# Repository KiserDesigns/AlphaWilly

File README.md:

Firmware built on this commit of Vial:

https://github.com/vial-kb/vial-qmk/commit/d4976853a3d72a370eeb24f6754e1618b5deb3bd

Newer Vial and QMK versions will need modification to firmware files.

PCB designed with Kicad 6.0.10, using various footprints and symbols with undetermined origin.

AlphaWetPCB/ is the Kicad PCB files

WilliamPlate/ is the Kicad Plate files

"William Plate.dxf" is the plate outline for laser cutting

alphawilly/ contains Vial and QMK firmware source

.uf2 file is the default firmware to flash.

GPL 3.0 License

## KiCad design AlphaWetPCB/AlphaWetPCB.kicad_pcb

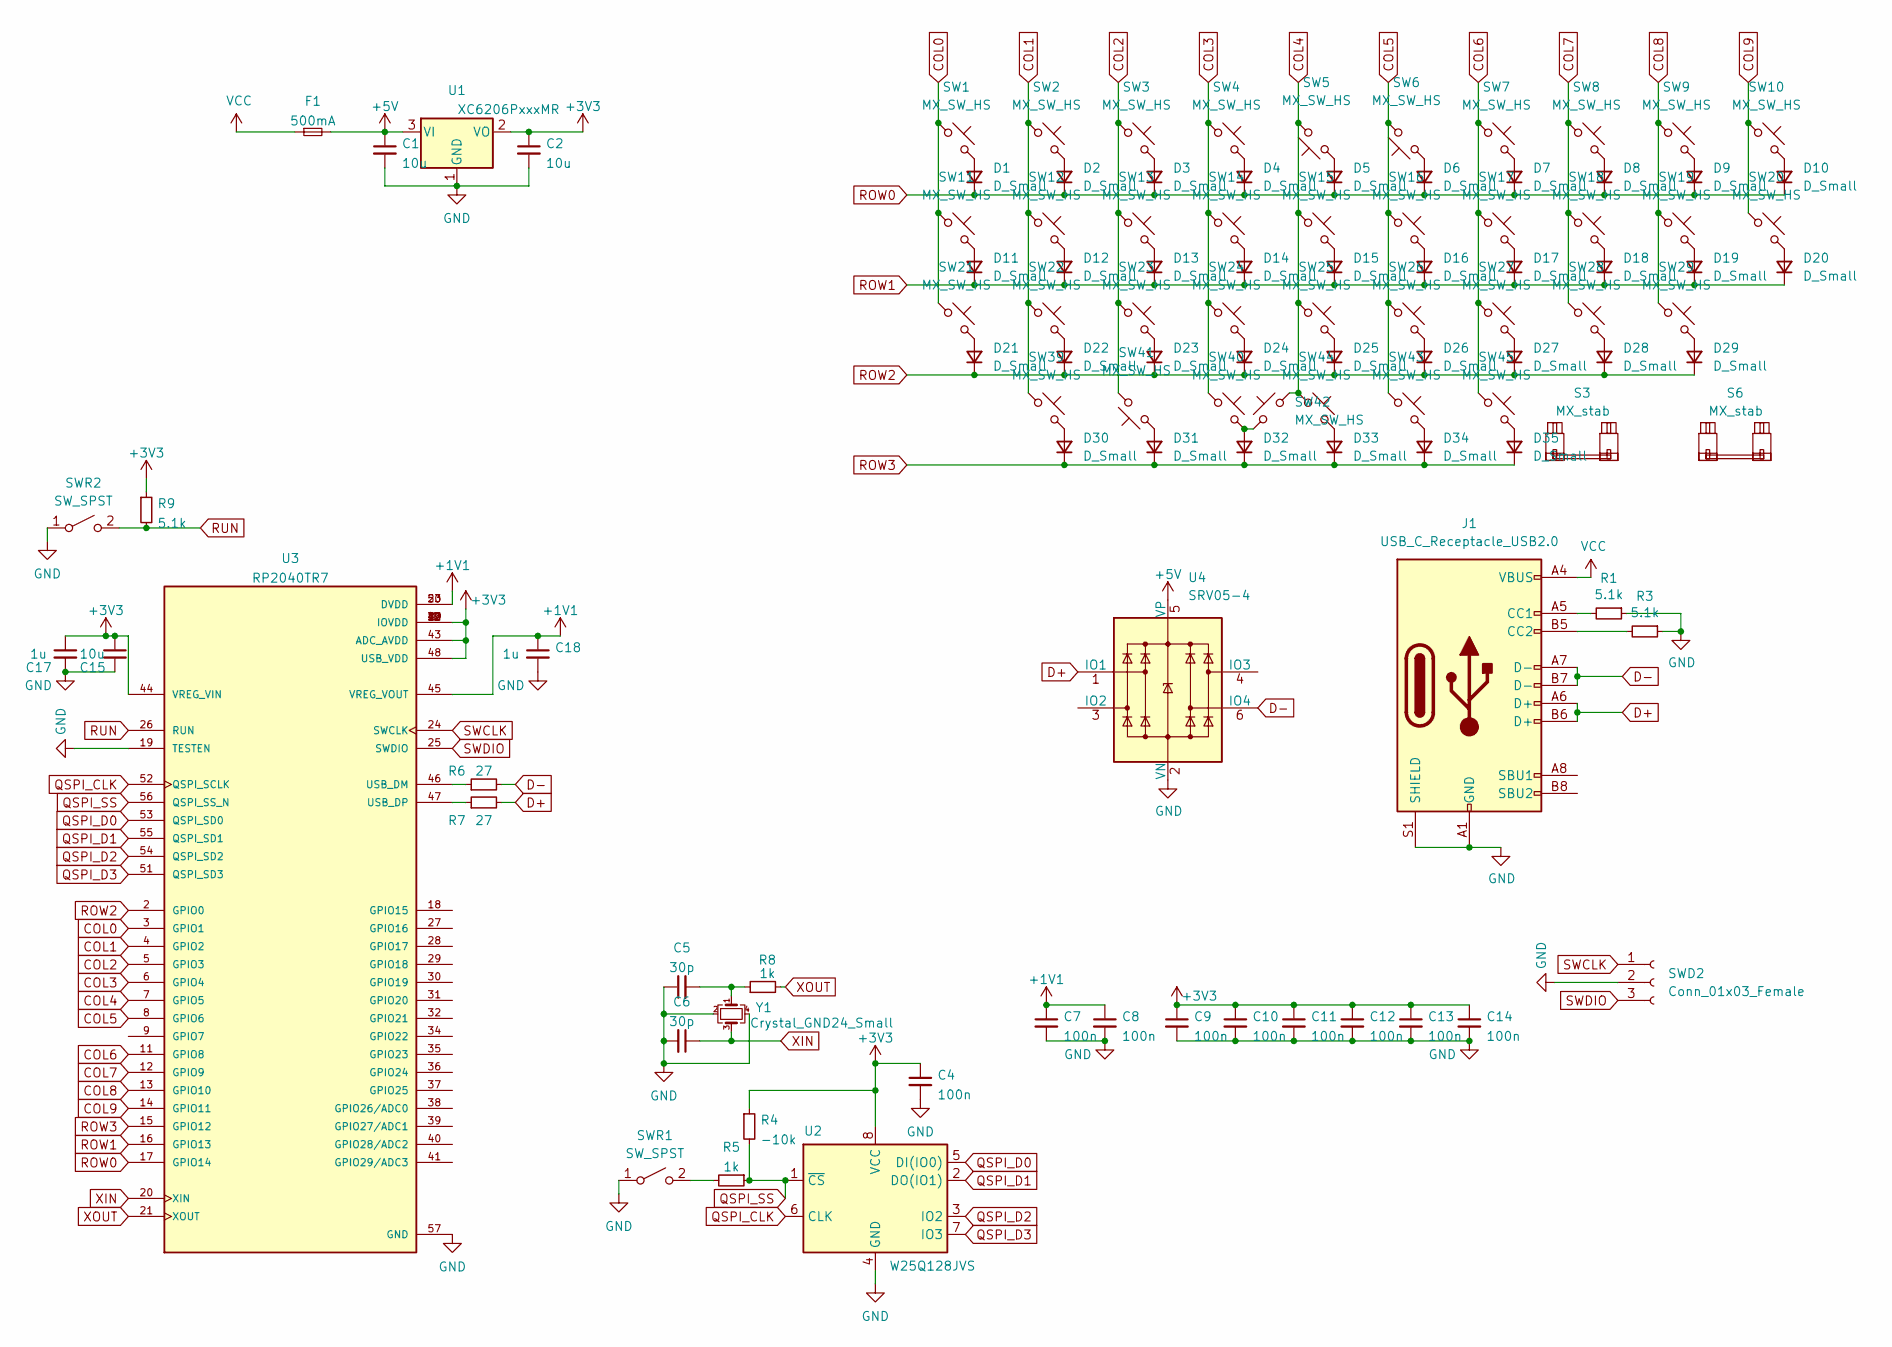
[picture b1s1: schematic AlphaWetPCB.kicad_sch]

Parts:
C1, C2, C15: 10u; C_0402_1005Metric
C4, C7, C8, C9, C10, C11, C12, C13, C14: 100n; C_0402_1005Metric
C5, C6: 30p; C_0402_1005Metric
C17, C18: 1u; C_0402_1005Metric
D1, D2, D3, D4, D5, D6, D7, D8, D9, D10, D11, D12, D13, D14, D15, D16, D17, D18, D19, D20, D21, D22, D23, D24, D25, D26, D27, D28, D29, D30, D31, D32, D33, D34, D35: D_Small; D_SOD-123
F1: 500mA; Fuse_1206_3216Metric
J1: USB_C_Receptacle_USB2.0; USB_C_Receptacle_HRO_TYPE-C-31-M-12
R1, R3: 5.1k; R_0603_1608Metric
R4: -10k; R_0603_1608Metric
R5, R8: 1k; R_0402_1005Metric
R6, R7: 27; R_0402_1005Metric
R9: 5.1k; R_0402_1005Metric
S3, S6: MX_stab; STAB_MX_3u
SW1, SW2, SW3, SW4, SW5, SW6, SW7, SW8, SW9, SW10, SW11, SW12, SW13, SW14, SW15, SW16, SW17, SW18, SW19, SW20, SW22, SW23, SW24, SW25, SW26, SW27, SW28, SW41, SW42, SW43: MX_SW_HS; SW_MX_HS_1u
SW21, SW29: MX_SW_HS; SW_MX_HS_1.5u
SW39, SW45: MX_SW_HS; SW_MX_HS_1.25u
SW40, SW44: MX_SW_HS; SW_MX_HS_1.75u
SWD2: Conn_01x03_Female; PinHeader_1x03_P2.54mm_Vertical
SWR1, SWR2: SW_SPST; SW_SPST_TL3342
U1: XC6206PxxxMR; SOT-23
U2: W25Q128JVS; SOIC-8_5.23x5.23mm_P1.27mm
U3: RP2040TR7; QFN40P700X700X90-57N; PARTREV 1.7.1
U4: SRV05-4; SOT-23-6-routable
Y1: Crystal_GND24_Small; Crystal_SMD_3225-4Pin_3.2x2.5mm

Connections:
+1V1: C7.1, C8.1, C18.1, U3.23 (DVDD), U3.45 (VREG_VOUT), U3.50 (DVDD)
+3V3: C2.1, C4.1, C9.1, C10.1, C11.1, C12.1, C13.1, C14.1, C15.1, C17.1, R4.1, R9.1, U1.2 (VO), U2.8 (VCC), U3.1 (IOVDD), U3.10 (IOVDD), U3.22 (IOVDD), U3.33 (IOVDD), U3.42 (IOVDD), U3.43 (ADC_AVDD), U3.44 (VREG_VIN), U3.48 (USB_VDD), U3.49 (IOVDD)
+5V: C1.1, F1.2, U1.3 (VI), U4.5 (VP)
COL0: SW1.1, SW11.1, SW21.1, U3.3 (GPIO1)
COL1: SW2.1, SW12.1, SW22.1, SW39.1, U3.4 (GPIO2)
COL2: SW3.1, SW13.1, SW23.1, SW41.2, U3.5 (GPIO3)
COL3: SW4.1, SW14.1, SW24.1, SW40.1, U3.6 (GPIO4)
COL4: SW5.2, SW15.1, SW25.1, SW42.2, SW44.1, U3.7 (GPIO5)
COL5: SW6.2, SW16.1, SW26.1, SW43.1, U3.8 (GPIO6)
COL6: SW7.1, SW17.1, SW27.1, SW45.1, U3.11 (GPIO8)
COL7: SW8.1, SW18.1, SW28.1, U3.12 (GPIO9)
COL8: SW9.1, SW19.1, SW29.1, U3.13 (GPIO10)
COL9: SW10.1, SW20.1, U3.14 (GPIO11)
D+: J1.A6 (D+), J1.B6 (D+), R7.2, U4.1 (IO1)
D-: J1.A7 (D-), J1.B7 (D-), R6.2, U4.6 (IO4)
GND: C1.2, C2.2, C4.2, C5.1, C6.2, C7.2, C8.2, C9.2, C10.2, C11.2, C12.2, C13.2, C14.2, C15.2, C17.2, C18.2, J1.A1 (GND), J1.A12 (GND), J1.B1 (GND), J1.B12 (GND), J1.S1 (SHIELD), R1.1, R3.1, SWD2.2, SWR1.1 (A), SWR2.1 (A), U1.1 (GND), U2.4 (GND), U3.19 (TESTEN), U3.57 (GND), U4.2 (VN), Y1.2, Y1.4
unnamed: C5.2, R8.1, Y1.1
unnamed: D1.2 (A), SW1.2
unnamed: D2.2 (A), SW2.2
unnamed: D3.2 (A), SW3.2
unnamed: D4.2 (A), SW4.2
unnamed: D5.2 (A), SW5.1
unnamed: D6.2 (A), SW6.1
unnamed: D7.2 (A), SW7.2
unnamed: D8.2 (A), SW8.2
unnamed: D9.2 (A), SW9.2
unnamed: D10.2 (A), SW10.2
unnamed: D11.2 (A), SW11.2
unnamed: D12.2 (A), SW12.2
unnamed: D13.2 (A), SW13.2
unnamed: D14.2 (A), SW14.2
unnamed: D15.2 (A), SW15.2
unnamed: D16.2 (A), SW16.2
unnamed: D17.2 (A), SW17.2
unnamed: D18.2 (A), SW18.2
unnamed: D19.2 (A), SW19.2
unnamed: D20.2 (A), SW20.2
unnamed: D21.2 (A), SW21.2
unnamed: D22.2 (A), SW22.2
unnamed: D23.2 (A), SW23.2
unnamed: D24.2 (A), SW24.2
unnamed: D25.2 (A), SW25.2
unnamed: D26.2 (A), SW26.2
unnamed: D27.2 (A), SW27.2
unnamed: D28.2 (A), SW28.2
unnamed: D29.2 (A), SW29.2
unnamed: D30.2 (A), SW39.2
unnamed: D31.2 (A), SW41.1
unnamed: D32.2 (A), SW40.2, SW42.1
unnamed: D33.2 (A), SW44.2
unnamed: D34.2 (A), SW43.2
unnamed: D35.2 (A), SW45.2
unnamed: J1.A5 (CC1), R1.2
unnamed: J1.B5 (CC2), R3.2
unnamed: R5.2, SWR1.2 (B)
unnamed: R6.1, U3.46 (USB_DM)
unnamed: R7.1, U3.47 (USB_DP)
QSPI_CLK: U2.6 (CLK), U3.52 (QSPI_SCLK)
QSPI_D0: U2.5 (DI(IO0)), U3.53 (QSPI_SD0)
QSPI_D1: U2.2 (DO(IO1)), U3.55 (QSPI_SD1)
QSPI_D2: U2.3 (IO2), U3.54 (QSPI_SD2)
QSPI_D3: U2.7 (IO3), U3.51 (QSPI_SD3)
QSPI_SS: R4.2, R5.1, U2.1 (~CS), U3.56 (QSPI_SS_N)
ROW0: D1.1 (K), D2.1 (K), D3.1 (K), D4.1 (K), D5.1 (K), D6.1 (K), D7.1 (K), D8.1 (K), D9.1 (K), D10.1 (K), U3.17 (GPIO14)
ROW1: D11.1 (K), D12.1 (K), D13.1 (K), D14.1 (K), D15.1 (K), D16.1 (K), D17.1 (K), D18.1 (K), D19.1 (K), D20.1 (K), U3.16 (GPIO13)
ROW2: D21.1 (K), D22.1 (K), D23.1 (K), D24.1 (K), D25.1 (K), D26.1 (K), D27.1 (K), D28.1 (K), D29.1 (K), U3.2 (GPIO0)
ROW3: D30.1 (K), D31.1 (K), D32.1 (K), D33.1 (K), D34.1 (K), D35.1 (K), U3.15 (GPIO12)
RUN: R9.2, SWR2.2 (B), U3.26 (RUN)
SWCLK: SWD2.1, U3.24 (SWCLK)
SWDIO: SWD2.3, U3.25 (SWDIO)
VCC: F1.1, J1.A4 (VBUS), J1.A9 (VBUS), J1.B4 (VBUS), J1.B9 (VBUS)
XIN: C6.1, U3.20 (XIN), Y1.3
XOUT: R8.2, U3.21 (XOUT)

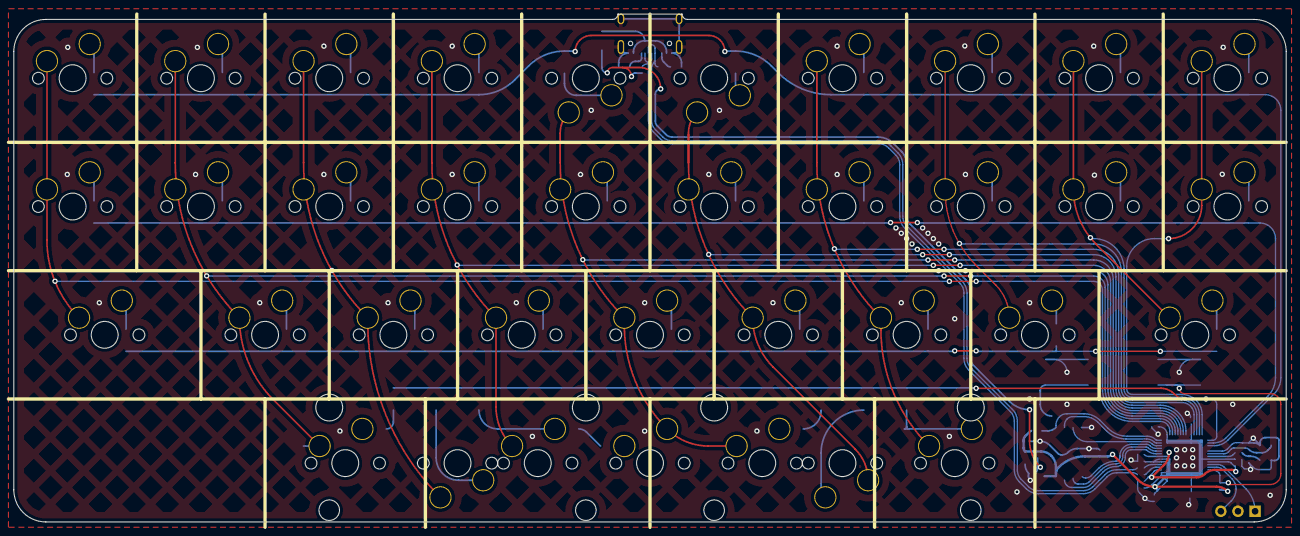
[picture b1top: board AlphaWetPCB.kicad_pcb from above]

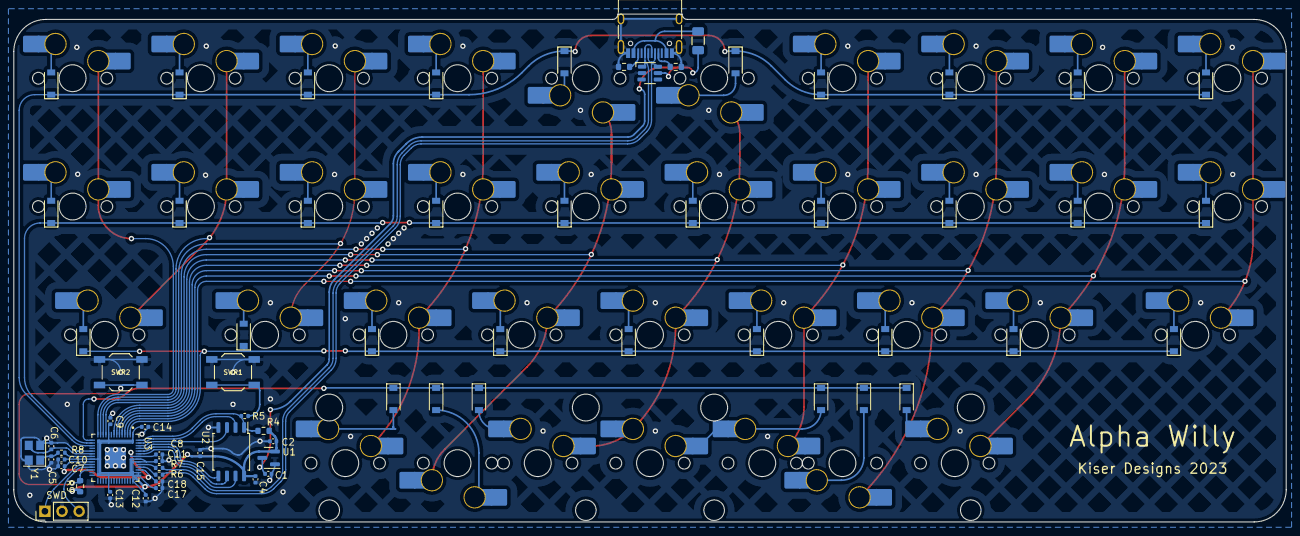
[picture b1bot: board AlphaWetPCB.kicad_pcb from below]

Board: 2 copper layers, 188.9 x 75.4 mm, 107 parts (105 on the bottom side), 73 nets.

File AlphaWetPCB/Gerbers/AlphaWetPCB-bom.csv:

Comment,Designator,Footprint,Quantity,JLCPCB Part #
SRV05-4,U4,SOT-23-6-routable,1,C85364
D_Small,"D3,D28,D27,D2,D35,D24,D9,D4,D33,D12,D7,D13,D6,D8,D22,D23,D29,D18,D16,D5,D32,D10,D1,D25,D19,D15,D20,D30,D31,D11,D14,D17,D21,D34,D26",D_SOD-123,35,C81598 
5.1k,"R1,R3,R9",R_0603_1608Metric,3,C23186
MX_SW_HS,"SW6,SW1,SW9,SW16,SW26,SW5,SW10,SW24,SW23,SW13,SW43,SW11,SW2,SW27,SW25,SW12,SW7,SW19,SW22,SW3,SW18,SW28,SW8,SW14,SW20,SW15,SW4,SW42,SW41,SW17",SW_MX_HS_1u,30,C2803348 
100n,"C11,C4,C10,C13,C8,C12,C9,C14,C7",C_0402_1005Metric,9,C1525
500mA,F1,Fuse_1206_3216Metric,1,C70077
-10k,R4,R_0603_1608Metric,1,
XC6206PxxxMR,U1,SOT-23,1,C5446 
1k,"R8,R5",R_0402_1005Metric,2,C11702
1u,"C17,C18",C_0402_1005Metric,2,C52923
10u,"C15,C2,C1",C_0402_1005Metric,3,C15525
USB_C_Receptacle_USB2.0,J1,USB_C_Receptacle_HRO_TYPE-C-31-M-12,1,C165948 
RP2040TR7,U3,QFN40P700X700X90-57N,1,C2040 
MX_SW_HS,"SW39,SW45",SW_MX_HS_1.25u,2,C2803348 
MX_SW_HS,"SW40,SW44",SW_MX_HS_1.75u,2,C2803348 
MX_SW_HS,"SW21,SW29",SW_MX_HS_1.5u,2,C2803348 
22,"R7,R6",R_0402_1005Metric,2,C25092
SW_SPST,"SWR1,SWR2",SW_SPST_TL3342,2,C318884 
30p,"C5,C6",C_0402_1005Metric,2,C277479
W25Q128JVS,U2,SOIC-8_5.23x5.23mm_P1.27mm,1,C97521
Crystal_GND24_Small,Y1,Crystal_SMD_3225-4Pin_3.2x2.5mm,1,C9002

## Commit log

2023-02-25 Add PCB and Plate files, JLC fab files in Gerbers
2023-02-25 Added Firmware Files
2023-02-25 Vial .uf2
